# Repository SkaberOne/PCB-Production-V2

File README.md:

# PCB Flow Production Suite

Application **Windows desktop** pour piloter le flux de production de cartes
électroniques (PCB) en atelier : de l'import des **BOM** (Bill of Materials)
jusqu'à la configuration des machines **Pick & Place**.

> **Version courante : 1.0.0** · Application autonome, installable, à mise à jour
> automatique. Stack : Electron · React 18 · FastAPI (Python) · SQLite / SQL Server.

---

## Ce que fait l'application

- **Import de BOM** (Eagle, Excel, CSV) avec révisions et historique
- **Harmonisation** des références composants entre formats fournisseurs
- **Bibliothèque** centralisée des composants et des BOM enregistrées
- **Calcul des besoins** composants par production
- **Préparation des commandes** composants avec export ERP (Excel)
- **Configuration des machines PnP** (feeders fixes/variables, chariots)
- **Coût de revient** par carte (« Prix carte »)
- **Suivi** des productions

---

## Installation

1. Télécharger le dernier installeur depuis la page
   **[Releases](https://github.com/SkaberOne/PCB-Production-V2/releases/latest)** :
   `PCB Flow Production Suite Setup x.y.z.exe`.
2. Lancer l'installeur (installation par utilisateur, **sans droits
   administrateur**), puis ouvrir l'app depuis le **raccourci Bureau**.
3. Double-clic → l'application démarre seule (le moteur de production est
   embarqué, rien d'autre à installer).

### Configuration de la base de données

Au premier lancement, un fichier de configuration est créé dans
`%APPDATA%\PCB Flow Production Suite\server\.env`.

- **Mono-poste** : une base **SQLite** locale (par défaut).
- **Multi-postes** : renseigner la connexion **SQL Server central** dans ce
  `.env` (prérequis : **ODBC Driver 17** sur chaque poste). Voir
  [`docs/guides/DEPLOYMENT.md`](docs/guides/DEPLOYMENT.md).

---

# Guide d'utilisation

Guide pratique pour l'opérateur. L'application accompagne une production, de
l'import de la BOM jusqu'à la configuration des machines Pick & Place.

## 1. Démarrer l'application

Double-cliquez sur le raccourci **PCB Flow Production Suite** (Bureau ou menu
Démarrer). Un court écran « Démarrage… » s'affiche, puis l'écran **Productions**
apparaît.

> Si l'écran « Backend indisponible » apparaît : la base de données n'est pas
> joignable. En multi-postes, vérifiez la connexion au serveur SQL (voir §8).

## 2. Comprendre l'écran

- **Barre du haut** : le **workflow en 5 étapes** (Productions → Import BOM →
  Revue BOM → Commande → Machine PnP). Les étapes se cochent en vert au fil de
  l'avancement.
- **Menu de gauche** :
  - *Workflow* : les 5 étapes de production.
  - *Bibliothèque* : Prix carte · BOM enregistrées · Base de données.
  - *Système* : Paramètres.
- **Bas de gauche** : la **production active** en cours.

## 3. Le workflow de production

**Étape 1 — Productions.** Point de départ. Créez une nouvelle production
(**+ Nouvelle production**) ou **chargez-en une existante** pour reprendre le
travail. La production active sert de contexte à toutes les étapes suivantes.

**Étape 2 — Import BOM.** Importez le ou les fichiers **BOM** de la carte (Eagle,
Excel, CSV). L'application **harmonise** les références et signale les
**composants manquants** (à compléter dans le catalogue) et les **empreintes
PnP** non renseignées. Complétez ce qui manque pour pouvoir continuer.

**Étape 3 — Revue BOM.** Passez la BOM **ligne par ligne** : vérifiez les
composants, **validez le stock** (la ligne passe au vert quand le besoin est
couvert), marquez les lignes non montées (DNP). Export CSV possible.

**Étape 4 — Commande.** L'application calcule la **liste des composants à
commander** à partir des BOM de la production (avec prix/disponibilité
fournisseurs si configurés). Saisissez les quantités reçues, puis **générez
l'export ERP** (Excel).

**Étape 5 — Machine PnP.** Configurez la ligne **Pick & Place** : machines,
**feeders** (fixes/variables), chariots, plan d'implantation. Cette étape prépare
le passage en machine.

## 4. Bibliothèque

- **Prix carte** : calcule le **coût de revient** d'une carte (matière + main
  d'œuvre + frais), en HT/TTC, et conserve un **historique de prix** par carte.
- **BOM enregistrées** : bibliothèque des BOM déjà importées (arborescence +
  détail des révisions). Bouton **Ouvrir** pour recharger une révision.
- **Base de données** : catalogue des composants, empreintes machine, règles de
  typage et d'harmonisation.

## 5. Paramètres

Référentiels et options : catalogue composants, empreintes machine, valeurs par
défaut de l'export ERP, connecteurs fournisseurs (Mouser, DigiKey…).

## 6. Mises à jour

L'application se met à jour **toute seule** : au démarrage, elle vérifie s'il
existe une nouvelle version ; vous pouvez aussi vérifier à tout moment via
**Aide → Rechercher les mises à jour**. Quand une mise à jour est prête, elle
propose de **redémarrer pour l'installer**.

## 7. Travail à plusieurs (postes partagés)

En multi-postes, tous les postes lisent et écrivent dans **la même base** (hébergée
sur le poste serveur). Concrètement :

- **Données communes** : ce qu'un poste enregistre est aussitôt dans la base, et
  les autres le verront — mais **pas en direct**. Si un collègue ajoute ou modifie
  une donnée pendant qu'un écran est déjà ouvert chez vous, **rechargez la page**
  (ou rouvrez l'écran) pour voir sa version à jour.
- **Édition de la même fiche au même moment** : l'application applique la règle du
  **« dernier qui enregistre gagne »**. Si deux personnes modifient **la même**
  fiche (même composant, même BOM…) en même temps, la dernière sauvegarde
  **écrase** celle de l'autre, sans avertissement. L'application ne détecte pas
  ce conflit.
- **Pas de risque pour la base** : la base elle-même n'est jamais corrompue ; le
  seul risque est de **perdre une modification** sur une fiche éditée à deux au
  même instant — cas rare à 2-3 personnes.

**En pratique** : répartissez-vous le travail (chacun ses productions / BOM),
rechargez une fiche avant de la modifier si un collègue pourrait y toucher, et
évitez d'éditer la même fiche à deux en même temps.

## 8. Bonnes pratiques

- Travaillez toujours **dans une production active** (chargez-la avant l'import).
- Complétez les **composants/empreintes manquants** signalés à l'import : ils
  bloquent les étapes suivantes.
- **Validez le stock** en Revue BOM avant de générer la commande.
- En multi-postes, **rechargez** un écran déjà ouvert pour voir les changements
  des collègues (cf. § 7).

## 9. En cas de souci

| Symptôme | Que faire |
|---|---|
| « Backend indisponible » au démarrage | Base injoignable. Multi-postes : vérifier le serveur SQL et le réseau ; pilote **ODBC Driver 17** installé. |
| « Network Error » / données qui ne chargent pas | Fermer puis relancer l'application. |
| Une production semble figée | Recharger la production depuis l'écran Productions. |
| Doute sur la version | Menu **Aide → À propos**. |

---

## Architecture

```
┌──────────── Poste Windows ────────────┐
│  PCB Flow Production Suite (Electron)  │
│   ├─ Interface React 18 (MUI)         │
│   └─ lance → backend FastAPI packagé  │
│        (PyInstaller, 127.0.0.1)       │
└───────────────────┬───────────────────┘
                    │ ODBC / SQLite
                    ▼
        Base SQLite locale  ou  SQL Server central
```

Chaque poste exécute son interface **et** son backend local ; seule la **donnée**
est centralisée (SQL Server) en multi-postes. Les mises à jour poussent
l'interface et le backend **d'un seul bloc** (electron-updater + GitHub Releases).

---

## Développement

Prérequis : Windows 10/11, Python 3.11+, Node.js 18+, Google Chrome.

> Aide-mémoire des lanceurs : [`LANCEMENT.md`](LANCEMENT.md).

```powershell
# Backend (crée .venv + dépendances)
.\serveur\INSTALLER_SERVEUR.bat
.\serveur\DEMARRER_SERVEUR_WEB.bat            # PROD web sur http://localhost:8000 (/docs)
.\serveur\_desktop\DEMARRER_SERVEUR.bat       # serveur dev classique (desktop)

# Frontend (React, port 3000)
.\client\_desktop\DEMARRER_CLIENT.bat

# Tests
.venv\Scripts\pytest serveur\src\tests\ -v
cd client\src\frontend ; npm test
```

### Construire & publier

```powershell
.\serveur\_desktop\CONSTRUIRE_SERVEUR.bat # backend → dist\pcb-flow-server
cd client\src\desktop ; npm run dist      # installeur (NSIS + portable)
cd client\src\desktop ; npm run publish   # publie une Release (GH_TOKEN requis)
```

Détails : [`docs/guides/DEPLOYMENT.md`](docs/guides/DEPLOYMENT.md) ·
check-list : [`docs/guides/Deploiement_Checklist_GoLive.md`](docs/guides/Deploiement_Checklist_GoLive.md).

---

## Documentation technique

| Fichier | Rôle |
|---|---|
| [`docs/Projet.md`](docs/Projet.md) | Description technique (vision, archi, modèle de données) |
| [`docs/guides/DEPLOYMENT.md`](docs/guides/DEPLOYMENT.md) | Build, packaging, mises à jour, base de données |
| [`docs/adr/`](docs/adr/) | Décisions d'architecture (ADR) |
| `STRUCTURE.md` | Organisation des dossiers du projet |
| `CLAUDE.md` | Process de travail assisté par IA |

---

*Outil métier interne — gestion de production PCB.*

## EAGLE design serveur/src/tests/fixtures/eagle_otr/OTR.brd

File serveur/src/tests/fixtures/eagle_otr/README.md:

# Fixtures — Import CAO Eagle (carte « OTR board Bicolor », KT240576C)

Jeu de calibration pour le parseur Eagle du **prompt 003**. Fournis par la planif via l'échange **E02**.

## Fichiers
- `OTR.brd`, `OTR.sch` — fichiers Eagle 9.6.2 réels (source BOM + centroïde).
- `OTR_machine_TOP.txt`, `OTR_machine_BOT.txt` — fichier de placement machine **ATTENDU**
  (format `Réf Valeur Empreinte X Y Angle Face`, `T`/`B`). Sert de **test de non-régression**.
- `parser_eagle_reference.py` — parseur de **référence VALIDÉ** (extrait 60 composants + centroïde).
  À porter dans `serveur/src/services/cao/`. **Pas besoin du repo privé `pcb-debug-assistant`.**

## Ce que le parseur doit produire (validé sur ce jeu)
- **Extraction complète** depuis le `.brd` : **60 éléments** (59 avec valeur + 1 logo `U$1` sans valeur).
  **Le parseur extrait TOUT** (aucune exclusion au niveau parseur).
- Par composant : `reference_item`, `value` (= `value_raw`), `footprint` (package Eagle), `x`, `y`,
  `rotation`, `face`.
- **Face** : rotation Eagle préfixée `M` (miroir) = **bottom**, sinon **top**.
- **MPN** (optionnel) : attribut `MANUFACTURER_PART_NUMBER` dans la techno du *device* (librairie du `.sch`).
  Présent pour ~6 composants (ICs, connecteurs).

## Transformation coordonnées carte → machine (VALIDÉE)
- **Top** : identité (x, y, rotation inchangés).
- **Bottom** : `x` inchangé ; **`y → H − y`** ; **`rotation → (rotation + 180) mod 360`**.
- **`H`** = hauteur de retournement, déduite du **contour** (layer 20 « Dimension ») du `.brd` :
  `H = y_min + y_max` du bounding box du contour. Sur OTR → **H = 34.20**.
- **Vérification exacte** via les `.txt` : pour tout composant *bottom*, `y_brd + y_machine = H` (= 34.20)
  et `rot_machine = (rot_brd + 180) mod 360`. (Le parseur peut donc s'auto-calibrer/valider sur ce jeu.)

## Exclusions du fichier machine = CURATION, pas une règle du parseur
Le fichier machine de référence a **49 lignes** (2 top + 47 bot) ; le parseur en produit ~60.
Absents du fichier machine : connecteurs J1-J6, test points SCL/SDA, logo `U$1`, **et C1/C4**
(→ **probable erreur d'export** côté CAO, confirmé par Eric ; à traiter comme curation, pas comme règle).

**Conséquence pour les tests :** le parseur extrait **tout** ; l'exclusion (connecteurs / TP / logo / DNP,
+ éventuels retraits manuels) se fait **en aval** (Revue BOM / règle de placement PnP). Le test de
transformation se fait sur les **références communes** au `.brd` et aux `.txt` — **ne pas** hard-fail
sur C1/C4.

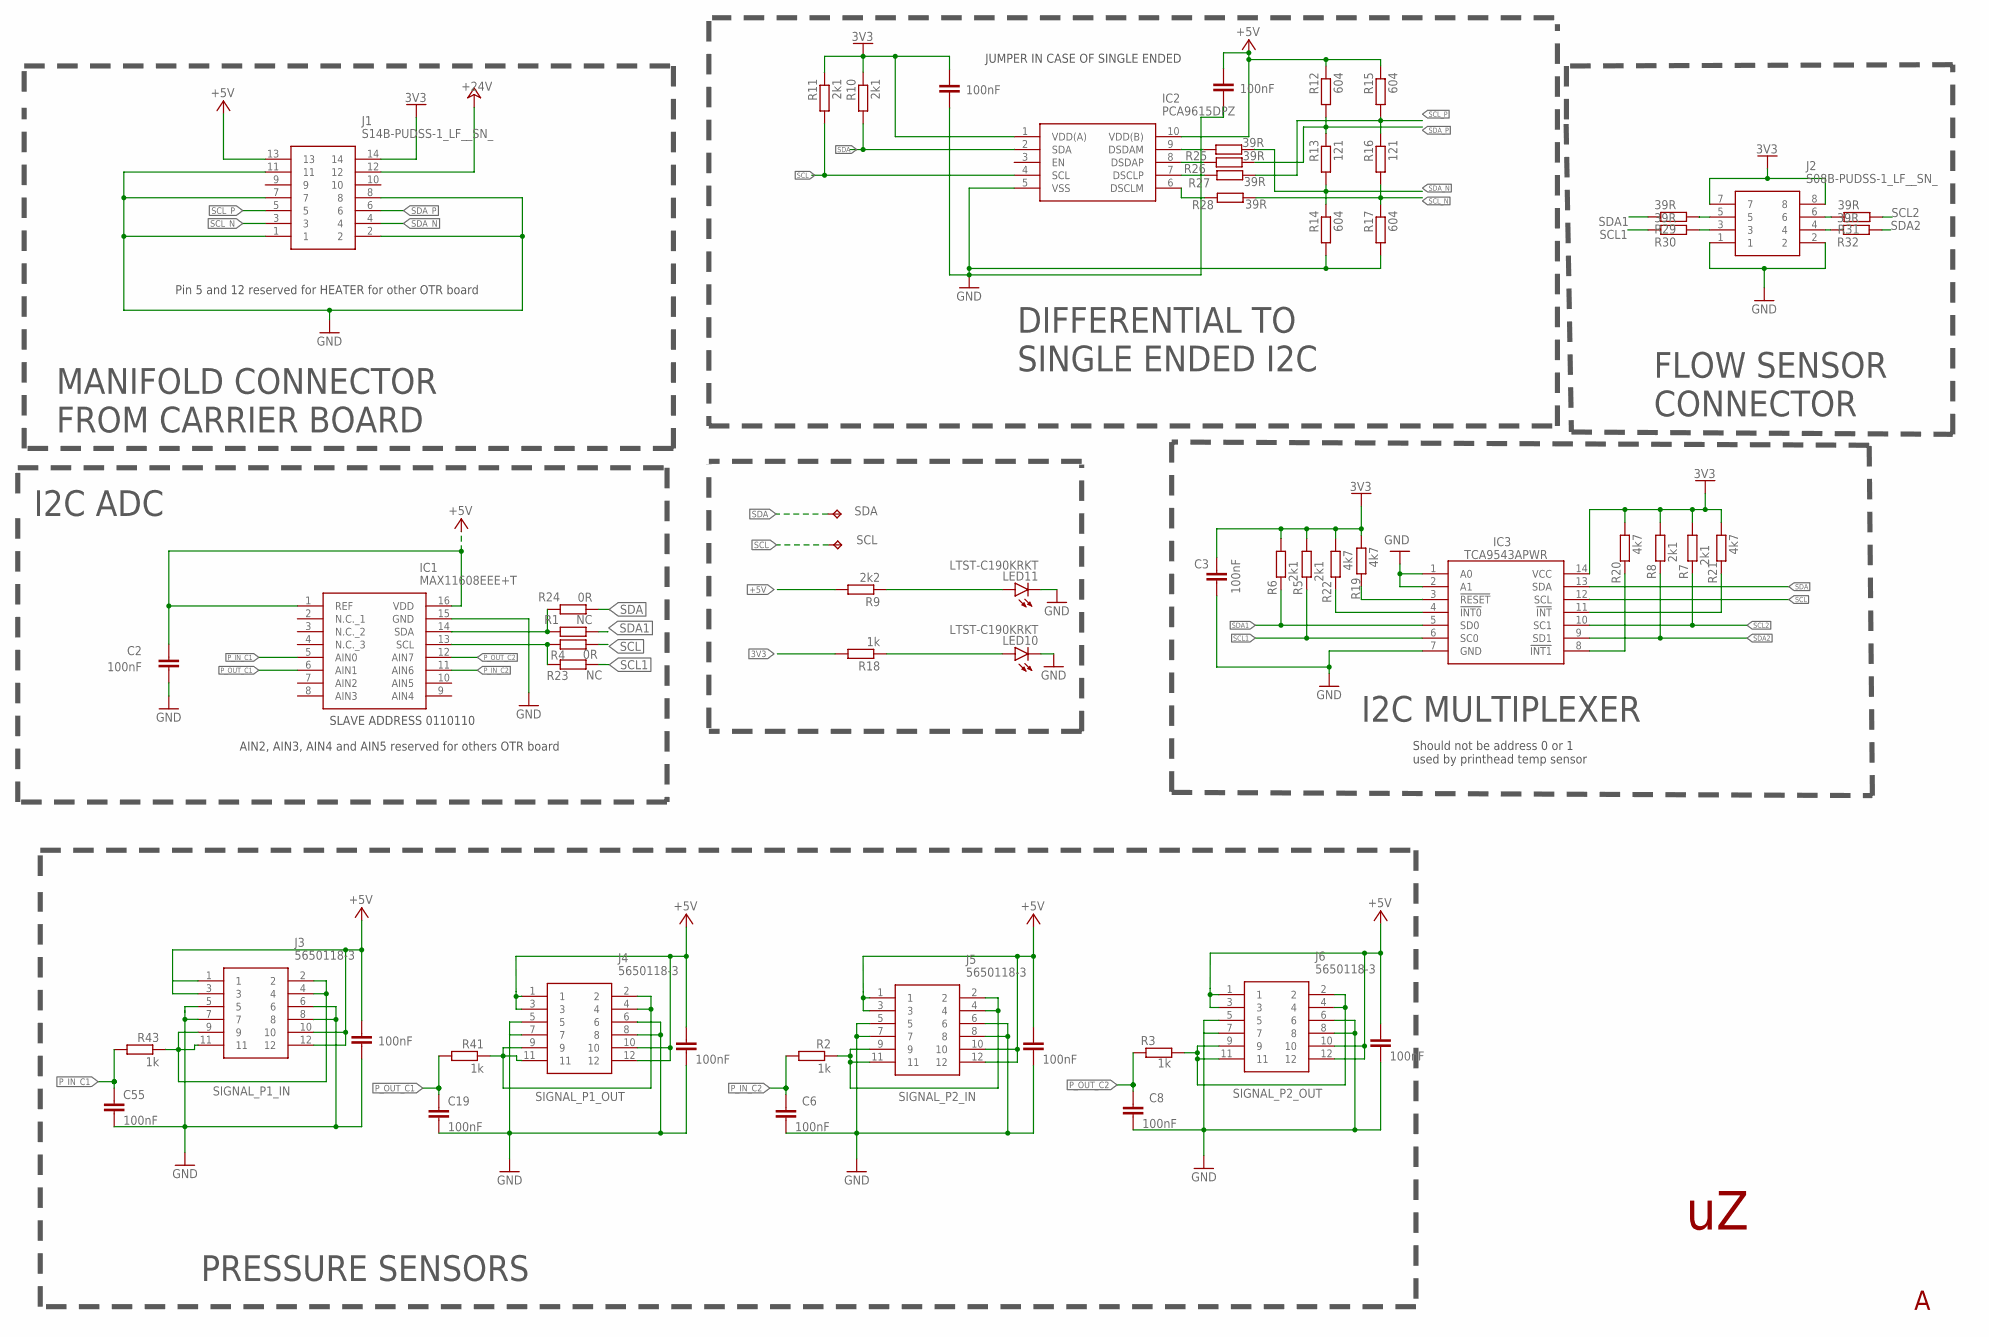
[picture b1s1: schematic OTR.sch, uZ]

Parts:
C1, C2, C3, C4, C5, C6, C7, C8, C16, C19, C24, C55: 100nF; C0603
IC1: MAX11608EEE+T; SOP64P602X175-16N
IC2: PCA9615DPZ; SOP50P490X110-10N
IC3: TCA9543APWR; SOP65P640X120-14N
J1: S14B-PUDSS-1_LF__SN_; S14BPUDSS1LFSN
J2: S08B-PUDSS-1_LF__SN_
J3, J4, J5, J6: 5650118-3; 56501183
LED10, LED11: LTST-C190KRKT; CHIPLED_0603
R1, R23: NC; R0603
R2, R3, R18, R41, R43: 1k; R0603
R4, R24: 0R; R0603
R5, R6, R7, R8, R10, R11: 2k1; R0603
R9: 2k2; R0603
R12, R14, R15, R17: 604; R0603
R13, R16: 121; R0603
R19, R20, R21, R22: 4k7; R0603
R25, R26, R27, R28, R29, R30, R31, R32: 39R; R0603
SCL: TEST_POINT
SDA: TEST_POINT

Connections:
3V3: C1.1, C3.2, IC2.1 (VDD(A)), IC3.14 (VCC), J1.14, J2.7, J2.8, R5.1, R6.1, R7.1, R8.1, R10.1, R11.1, R18.2, R19.2, R20.2, R21.2, R22.2
+5V: C2.1, C4.1, C5.1, C7.1, C16.1, C24.1, IC1.1 (REF), IC1.16 (VDD), IC2.10 (VDD(B)), J1.13, J3.1, J3.3, J3.10, J3.12, J4.1, J4.3, J4.10, J4.12, J5.1, J5.3, J5.10, J5.12, J6.1, J6.3, J6.10, J6.12, R9.2, R12.1, R15.1
+24V: J1.12
GND: C1.2, C2.2, C3.1, C4.2, C5.2, C6.2, C7.2, C8.2, C16.2, C19.2, C24.2, C55.2, IC1.15 (GND), IC2.5 (VSS), IC3.1 (A0), IC3.2 (A1), IC3.7 (GND), J1.1, J1.2, J1.7, J1.8, J1.11, J2.1, J2.2, J3.5, J3.6, J3.7, J3.8, J4.5, J4.6, J4.7, J4.8, J5.5, J5.6, J5.7, J5.8, J6.5, J6.6, J6.7, J6.8, LED10.C, LED11.C, R14.2, R17.2
unnamed: IC3.8 (!INT1), R20.1
unnamed: IC3.11 (!INT), R21.1
unnamed: IC3.4 (!INT0), R22.1
unnamed: LED11.A, R9.1
unnamed: LED10.A, R18.1
unnamed: IC3.3 (!RESET), R19.1
unnamed: IC2.9 (DSDAM), R25.1
unnamed: J2.5, R29.2
unnamed: IC1.14 (SDA), R1.2, R24.2
unnamed: IC1.13 (SCL), R4.2, R23.2
unnamed: IC2.8 (DSDAP), R26.1
unnamed: IC2.7 (DSCLP), R27.1
unnamed: IC2.6 (DSCLM), R28.1
unnamed: J2.3, R30.2
unnamed: J2.4, R32.1
unnamed: J2.6, R31.1
P_IN_C1: C55.1, IC1.5 (AIN0), R43.2
P_IN_C2: C6.1, IC1.11 (AIN6), R2.2
P_OUT_C1: C19.1, IC1.6 (AIN1), R41.2
P_OUT_C2: C8.1, IC1.12 (AIN7), R3.2
SCL: IC2.4 (SCL), IC3.12 (SCL), R4.1, R11.2, SCL.P$1
SCL1: IC3.6 (SC0), R5.2, R23.1, R30.1
SCL2: IC3.10 (SC1), R7.2, R31.2
SCL_N: J1.3, R16.2, R17.1, R28.2
SCL_P: J1.5, R15.2, R16.1, R27.2
SDA: IC2.2 (SDA), IC3.13 (SDA), R10.2, R24.1, SDA.P$1
SDA1: IC3.5 (SD0), R1.1, R6.2, R29.1
SDA2: IC3.9 (SD1), R8.2, R32.2
SDA_N: J1.4, R13.2, R14.1, R25.2
SDA_P: J1.6, R12.2, R13.1, R26.2
SIGNAL_P1_IN: J3.2, J3.4, J3.9, J3.11, R43.1
SIGNAL_P1_OUT: J4.2, J4.4, J4.9, J4.11, R41.1
SIGNAL_P2_IN: J5.2, J5.4, J5.9, J5.11, R2.1
SIGNAL_P2_OUT: J6.2, J6.4, J6.9, J6.11, R3.1

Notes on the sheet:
SLAVE ADDRESS 0110110
JUMPER IN CASE OF SINGLE ENDED
MANIFOLD CONNECTOR FROM CARRIER BOARD
I2C ADC
PRESSURE SENSORS
DIFFERENTIAL TO SINGLE ENDED I2C
FLOW SENSOR CONNECTOR
I2C MULTIPLEXER
Should not be address 0 or 1 used by printhead temp sensor
AIN2, AIN3, AIN4 and AIN5 reserved for others OTR board
Pin 5 and 12 reserved for HEATER for other OTR board

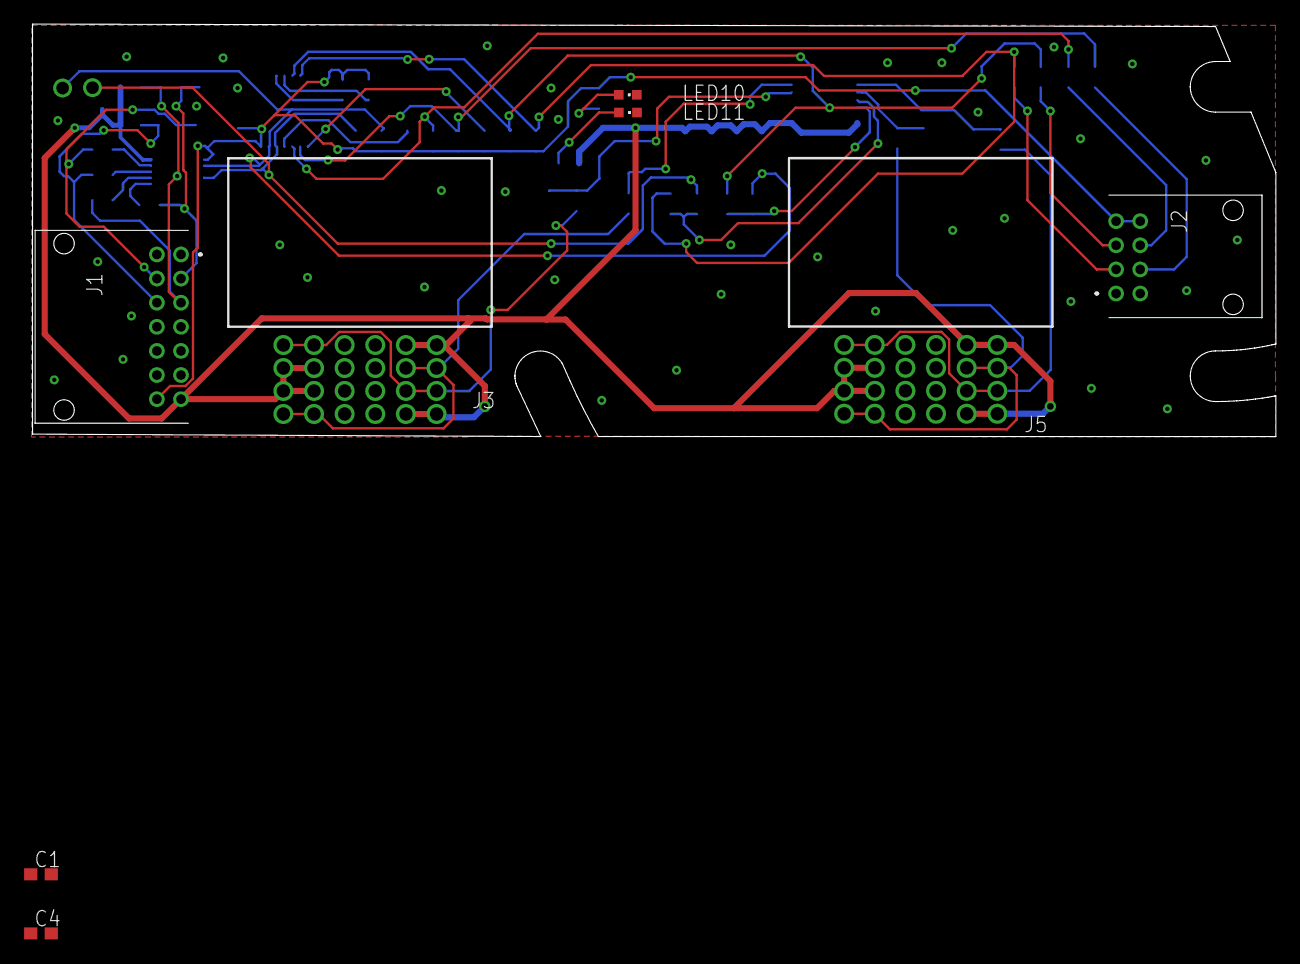
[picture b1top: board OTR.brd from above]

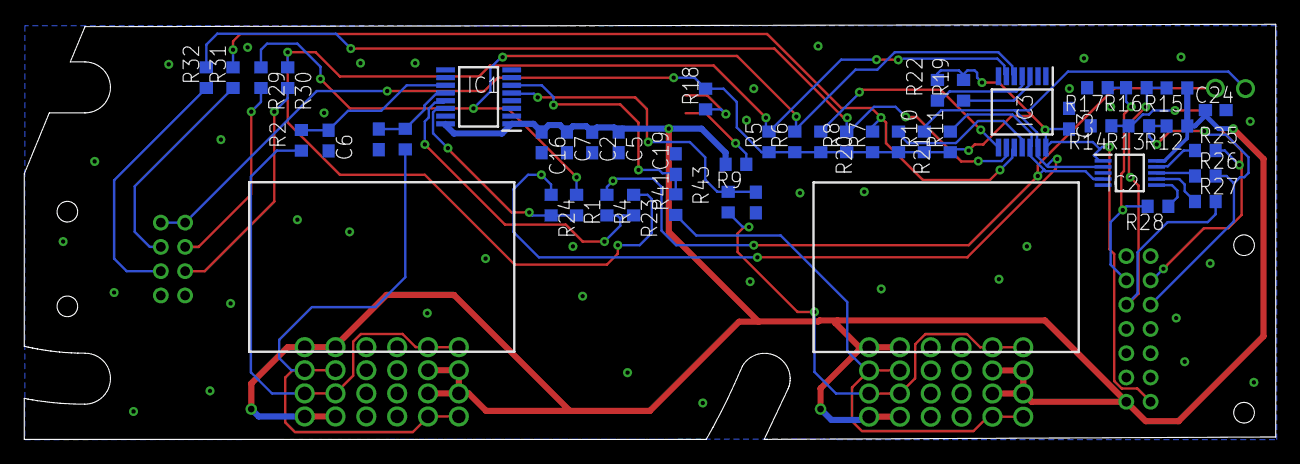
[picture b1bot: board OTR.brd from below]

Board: 2 copper layers, 103.1 x 34.2 mm, 60 parts (49 on the bottom side), 37 nets.

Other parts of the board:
U$1: LOGO_KT_7/7

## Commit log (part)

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2026-05-29 chore: snapshot initial avant audit-restructure
2026-05-29 fix: bugs preexistants decouverts apres restructuring
    - config.py: logger.i tronque a la fin -> logger.info
    (le fichier original etait coupe)
    - conftest.py: force DATABASE_URL sqlite://:memory: avant import
    (sinon le default SQL Server tente d'importer pyodbc)
    - conftest.py: vide API_KEY pour les tests (mode open)
    - Install httpx (dependance manquante pour starlette.testclient)
2026-06-02 feat(bom): menu multi-selection des BOM pour une production + fix ouverture depuis la bibliotheque
    - BomPickerDialog: selection multiple des BOM enregistrees a rattacher a la production active (bouton 'Choisir des BOM').
    - Cable le bouton 'Charger une BOM' de l'etat vide (auparavant inactif).
    - BomViewerPage lit desormais le parametre d'URL ?revision= : le bouton 'Ouvrir' de la bibliotheque charge bien la revision dans la session.
    - Tests: BomPickerDialog (2), ?revision= (2); corrige 2 tests stale de BomViewerPage (production active requise pour afficher le plan de travail).
2026-06-02 feat(datasheets): matching par champ value + boitier base prioritaire
    - select_component: match aussi sur COMPONENTS.value (reference=ID interne, mpn quasi vide); comparaison normalisee avec garde anti-faux-positif
    - process_pdf: boitier resolu via --package > package en base > detection PDF
    - eia481: ajout SOT-25/SOT-26
    - tests: matching value + non-confusion (31 pytest verts)
    Resultat dry-run dev.db: 31/32 datasheets matchees, 15 composants completables (pitch/largeur/feeder via EIA-481).
2026-06-02 refonte(v2): consolidation design system - palette unifiee (slate->zinc, indigo->emeraude, surfaces->#18181b, rouges/bleus->tokens), onglet vert, ConfirmDialog destructifs
2026-06-03 feat(suppliers): connecteurs API Mouser/DigiKey + offres prix/dispo
    Interface SupplierConnector commune + adaptateurs Mouser (cle) et DigiKey (OAuth2 2-legged), cache SUPPLIER_OFFERS (TTL 24h) + refresh temps reel, tri multi-fournisseurs (moins cher / priorise), revu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
2026-06-03 feat(commande): receptions + tableau d'approvisionnement unifie
    Table COMMAND_RECEIPTS (migration i3d4e5f6a7b8) + production_command_service (sync/get/set receipt, summary_with_receipts), routes sync/command/receipts. Page commande refondue : un seul tableau (BOM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
2026-06-04 feat(bibliotheque): page Base de donnees a 4 onglets + identifiants API fournisseurs
    - SettingsPage scinde: la gestion des donnees (composants, empreintes, regles, MPN) part dans Bibliotheque > Base de donnees (route /base-donnees, 4 onglets)
    - BaseDeDonneesPage reduit a une coquille (52 l.); panneaux autonomes EmpreintesPanel/ComposantsPanel/ReglesTypePanel dans components/library
    - Onglet Empreintes: tableau des empreintes chargees
    - Nouveau SettingsPage epure + SupplierApiSettings (Mouser/DigiKey, type d'auth selectionnable, secrets masques)
    - Backend: store supplier_credentials (gitignore), endpoints GET/PUT /supplier-offers/credentials, build_connectors overlay .env, test ajoute
    -
2026-06-04 docs: audit complet pre-deploiement 2026-06-04 (live + code)
2026-06-04 docs: audit + plan d'action deploiement (multi-postes SQL Server)
2026-06-04 feat(machine-pnp): dialogue de configuration machine (plan d'implantation)
    Nouveau MachineConfigDialog: affecte/detache une production, reordonne la sequence BOM, valide/devalide l'ordre de fabrication, calcule et visualise l'implantation feeders (slot-strip avant/arriere +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
2026-06-04 feat(machine-pnp): CRUD machine + chariot dans la V2 (parite V1)
    Nouveau MachineCrudDialogs (creation machine, creation/edition chariot) branche dans MachinePnpWorkspace avec boutons Nouvelle machine / Nouveau chariot et edition chariot. La V2 atteint la parite fo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
2026-06-04 feat(machine-pnp): filtrage du plan par revision BOM + commun/implantation (P0.2)
    Expose dans MachineConfigDialog les capacites deja calculees par useMachineConfig: chips de selection par BOM (handleToggleMachineBomRevision) et filtre Tous/Communs/Implantation avec compteurs. La t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
2026-06-04 refactor(machine-pnp): extrait les derivations feeders fixes (<300 l.) [P1.5]
    useFixedFeeders (375 l.) -> 241 l. : etat filtres/tri + lignes filtrees + chips + options deplaces dans useFixedFeederDerived (pure presentation, sans effet reseau). Comportement inchange.
2026-06-04 feat(machine-pnp): refonte vue machine - topologie reelle + couleur par taille feeder [Phase 3]
    Slot-strip redessine: couleur = taille de feeder (8/12/16 mm, palette sombre), numero toujours visible, reference au survol (et en clair <=24 slots/rampe), anneau de selection. MachineImplantationPan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
2026-06-04 feat(machine-pnp): panneau 'a placer a la main' + badges TOP/BOT [Phase 3]
    Nouveau ManualPlacementPanel: affiche les composants renvoyes par le backend (manual_placement_components) avec footprint, taille feeder (pastille couleur), nb de poses, et le total d'emplacements li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
2026-06-04 test(machine-pnp): smoke test de rendu V2 (MachinePnpWorkspace) - filet pour refactors
2026-06-05 feat(machine-pnp): promotion de la V2 en defaut + retrait de la banniere WIP [#3]
    Flag machinePnpPlan defaut ON (la page Machine PnP affiche desormais la V2). Banniere 'construction en cours' retiree, titre simplifie 'Plan d'implantation'. MachinePnpPage.test force le flag OFF pou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
2026-06-05 feat(machine-pnp): slots 2 couleurs fixe/mobile, placement fixe arriere, fondation nozzles
    - Recolor slots par placement_group (FIXED=ambre / DYNAMIC=emeraude) au lieu de la taille feeder; legende Fixe/Mobile/Libre
    - Placement: feeders fixes remplis depuis l'arriere (positions hautes), mobiles depuis l'avant (assign_entry from_back)
    - Fondation nozzles: champ num_nozzles (modele+migration+schemas+service+routes+serialize), helper utils/nozzles.py (deduction par feeder_size, NOZZLE_REACH_BY_CLASS vide a remplir apres tests physiq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
    - Frontend: champ num_nozzles (Create/EditMachineDialog), machineNumNozzles selector, composant NozzleHead (
2026-06-05 feat(machine-pnp): selection de face -> config PnP recalculee par face
    - Backend: plan par face garde TOUTES les faces dans ordered_boms (selecteur UI complet), ne scope que l'usage/affectations/a-la-main a la face choisie
    - Frontend: loadMachineProductionPlan(machineId, productionId, bomRevisionId) -> query ?bom_revision_id ; l'effet de chargement refetch le plan quand la face selectionnee change
    - UI: chips 'Face a produire' (avec TOP/BOT) recalculent la config PnP de la face; clic a nouveau = retour plan global
    Tests: pytest 22/22, jest MachinePnp 9/9
2026-06-05 feat(machine-pnp): selection de face dans le tableau de sequence (retrait des chips)
    - Les lignes du tableau de sequence de production sont cliquables: clic = selectionner/deselectionner la face -> recalcul de la config PnP de cette face ; ligne selectionnee surlignee (bord vert)
    - Boutons monter/descendre: stopPropagation pour ne pas declencher la selection
    - Retrait du bloc de chips 'Face a produire' + sous-filtre au-dessus du pick and place (selection deplacee dans le tableau)
    Tests: jest MachinePnp 9/9
2026-06-06 fix(erp-export): laisser Reference KT vide
    Champ interne societe, rempli a la main dans l'ERP apres import.
    Le pre-remplissage avec COMPONENTS.reference (audit 2026-06-03 §6.2)
    ne correspond pas au processus reel d'achat.
2026-06-08 test(migrations): reparer harness + portabilite SQLite (partiel)
    - REVISION_CHAIN remise a jour (10 -> 17 revisions, head k5f6a7b8c9d0)
    - harness: fn passe via opts a configure(), proxy op via Operations.context
    (API Alembic 1.18 ; run_migrations(fn=) etait ignore)
    - 2 migrations FK converties en batch_alter_table (ALTER natif SQL Server,
    copy-move SQLite)
    16 -> 8 echecs. Les 8 restants exposent une derive reelle : 10 tables des
2026-06-08 feat(machine-pnp): numérotation rail arrière + placement bilatéral + nozzles bornés
    - Config par machine `feeder_back_order` (ASC/DESC) : la colonne Feeder de
    l'export est mappée au numéro physique du rail arrière (ASC 41→80 = machine A,
    DESC 80→41 = machine B). L'avant reste 1→N/2. Migration m7b8c9d0e1f2 + champ
    modèle/schéma/route/service/sérialiseur + sélecteur dans les dialogues machine.
    - Placement auto par rampe : feeders dynamiques sur la rampe avant, fixés sur la
    rampe arrière (repli sur l'autre rampe si pleine).
2026-06-09 feat(machine): menu deroulant categories existantes pour chariot CATEGORY
    Le champ Categorie cible du chariot devient un Autocomplete alimente par GET /api/bom/categories (freeSolo: saisie libre conservee).
2026-06-09 chore(git): mise au propre workflow, CI et gitignore
2026-06-09 refactor(ui): densifier coque, tableaux et en-tetes de page
2026-06-10 chore(build): builds sans admin via CSC_IDENTITY_AUTO_DISCOVERY=false
    Pose la variable dans les scripts dist/dist:portable/publish pour eviter l'extraction winCodeSign (liens symboliques macOS) qui exigeait le Mode Developpeur/admin. MAJ doc deploiement + checklist (in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
2026-06-10 docs: README v1.0 + manuel utilisation + note relance auto a reprendre
2026-06-10 chore: retire fichier temporaire publish_done.txt + gitignore artefacts publish
2026-06-12 fix(mpn): recherche en ligne par sous-lots de 25
    Evite le timeout axios 30s sur gros lots (ex. 200 MPN). MpnEnrichmentPanel decoupe les component_ids en tranches de 25, requetes enchainees avec progression visible, pause anti-quota entre lots, time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
2026-06-12 chore(release): bump version 1.0.2 (test deploiement assiste)
2026-06-15 feat(deploiement): signature de code interne (cert auto-signe)
    #5: make_signing_cert.ps1 (cert code-signing auto-signe + export pfx/cer), trust_cert.ps1 (approbation Root+TrustedPublisher par poste), scripts npm dist:signed/publish:signed (signent via CSC_LINK),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
2026-06-15 fix(deploiement): lecture dynamique du pont electronAPI (DatabaseSettings)
    dbConfigApi etait capture au chargement du module -> undefined si le preload/le test definit window.electronAPI apres. Lu dynamiquement via getDbApi(). 5/5 tests DatabaseSettings verts.
2026-06-16 chore(release): bump 1.0.3 (correctifs encodage installeur + alembic)
2026-06-16 fix(db): compat SQL Server (.is_(True/False) -> ==) + ecran config DB sur erreur backend (1.0.6)
2026-06-19 fix(sql): dnp.isnot(True) -> forme NULL-safe (T-SQL, debloque Commande + Prix carte)
2026-06-19 docs(roadmap): T-003 (handoff import->revue perd 2e face) en prochain chantier P1
2026-06-19 docs: synchro T-003 corrige (cae93ef) + entree session 5 changelog
2026-06-19 fix(revue): bandeau avertissements distinct du chip a verifier (T-006)
2026-06-30 docs(release): checklist de release correctifs test terrain (T-001 a T-008)
